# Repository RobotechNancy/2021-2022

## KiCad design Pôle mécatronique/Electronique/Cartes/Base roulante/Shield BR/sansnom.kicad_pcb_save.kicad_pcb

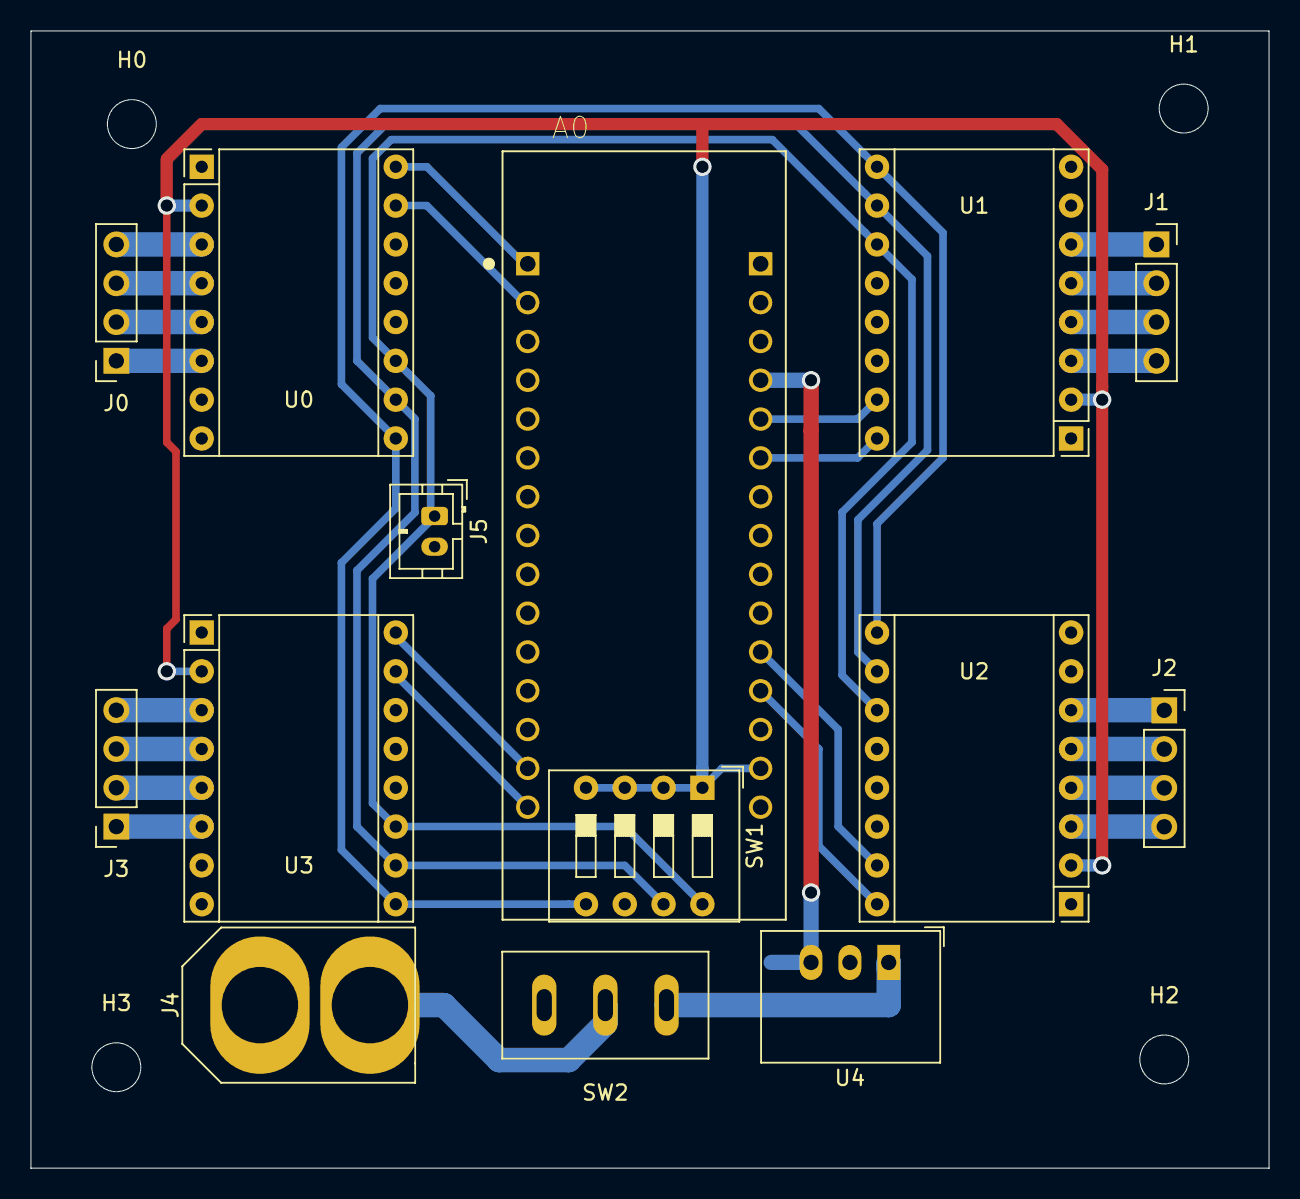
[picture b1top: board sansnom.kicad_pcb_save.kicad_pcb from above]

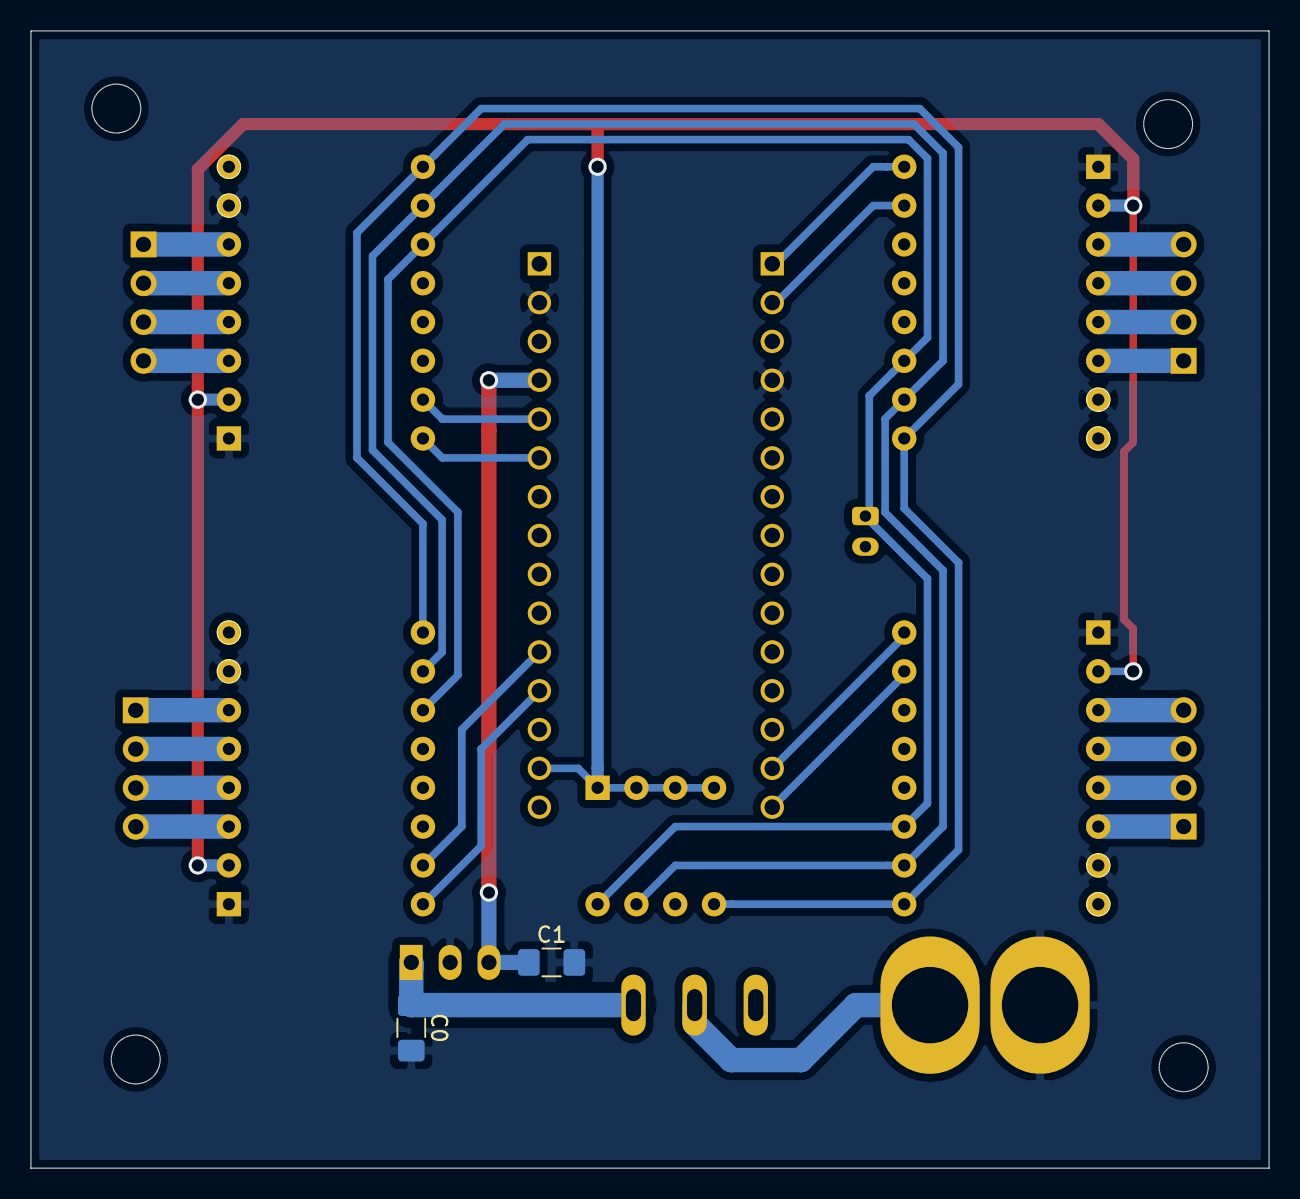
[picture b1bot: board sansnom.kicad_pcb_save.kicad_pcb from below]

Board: 2 copper layers, 81.0 x 74.4 mm, 20 parts (2 on the bottom side), 34 nets.

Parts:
A0: NUCLEO-F303K8; MODULE_NUCLEO-F303K8
C0, C1: 10u; C_1206_3216Metric_Pad1.42x1.75mm_HandSolder
H0, H1, H2, H3: MountingHole; MountingHole_3.2mm_M3
J0, J1, J2, J3: Conn_01x04_Female; PinSocket_1x04_P2.54mm_Vertical
J4: XT60
J5: Conn_01x02_Female; JST_PH_B2B-PH-K_1x02_P2.00mm_Vertical
SW1: SW_DIP_x04; SW_DIP_SPSTx04_Slide_9.78x12.34mm_W7.62mm_P2.54mm
SW2: SW_Push_SPDT; Switch_3_Pin
U0, U1, U2, U3: TMC2208; TMC_2208_BOB
U4: R-78E5.0-0.5; Converter_DCDC_RECOM_R-78E-0.5_THT

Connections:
+5V: A0.4.4, C1.1, U4.3
+BATT: C0.1, SW2.1, U0.8, U1.8, U2.8, U3.8, U4.1
CAN_Rx: A0.3.13, J5.2
CAN_Tx: A0.3.5, J5.1
Dir0: A0.3.1, U0.9
Dir1: A0.4.6, U1.9
Dir2: A0.4.12, U2.9
Dir3: A0.3.14, U3.9
EN: SW1.5, U0.16, U1.16, U2.16, U3.16
GND: A0.3.4, A0.4.2, C0.2, C1.2, J4.1, U0.1, U0.7, U1.1, U1.7, U2.1, U2.7, U3.1, U3.7, U4.2
M1: SW1.7, U0.15, U1.15, U2.15, U3.15
M2: SW1.8, U0.14, U1.14, U2.14, U3.14
unnamed: J0.1, U0.6
unnamed: J0.2, U0.5
unnamed: J0.3, U0.4
unnamed: J0.4, U0.3
unnamed: J1.1, U1.6
unnamed: J1.2, U1.5
unnamed: J1.3, U1.4
unnamed: J1.4, U1.3
unnamed: J2.1, U2.6
unnamed: J2.2, U2.5
unnamed: J2.3, U2.4
unnamed: J2.4, U2.3
unnamed: J3.1, U3.6
unnamed: J3.2, U3.5
unnamed: J3.3, U3.4
unnamed: J3.4, U3.3
unnamed: J4.2, SW2.2
Stp0: A0.3.2, U0.10
Stp1: A0.4.5, U1.10
Stp2: A0.4.11, U2.10
Stp3: A0.3.15, U3.10
Vio: A0.4.14, SW1.1, SW1.2, SW1.3, SW1.4, U0.2, U1.2, U2.2, U3.2

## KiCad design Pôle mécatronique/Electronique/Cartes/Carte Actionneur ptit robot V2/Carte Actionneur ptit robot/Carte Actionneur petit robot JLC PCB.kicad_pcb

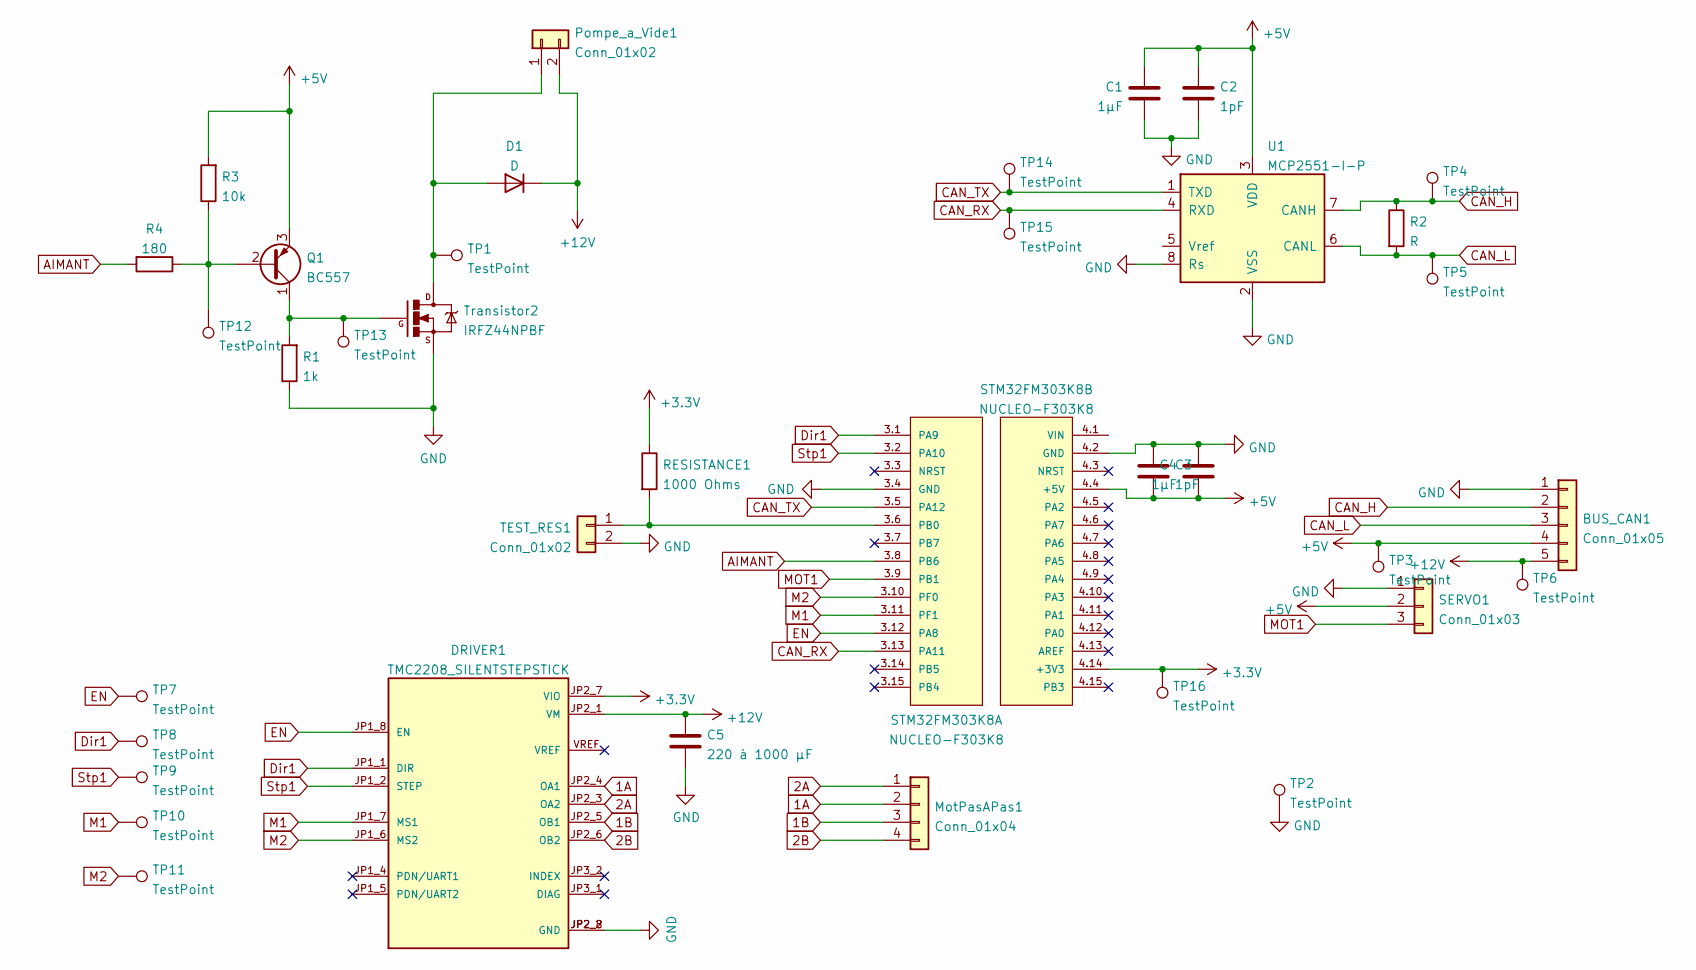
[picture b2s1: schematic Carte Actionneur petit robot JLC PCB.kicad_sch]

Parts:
BUS_CAN1: Conn_01x05; JST_PH_B5B-PH-K_1x05_P2.00mm_Vertical
C1, C4: 1µF; C_1206_3216Metric
C2, C3: 1pF; C_1206_3216Metric
C5: 220 à 1000 µF; CP_Radial_D8.0mm_P3.50mm
D1: D; D_A-405_P12.70mm_Horizontal
DRIVER1: TMC2208_SILENTSTEPSTICK; MODULE_TMC2208_SILENTSTEPSTICK
MotPasAPas1: Conn_01x04; PinSocket_1x04_P2.54mm_Vertical
Pompe_a_Vide1: Conn_01x02; JST_PH_B2B-PH-K_1x02_P2.00mm_Vertical
Q1: BC557; TO-92_Inline
R1: 1k; R_Axial_DIN0207_L6.3mm_D2.5mm_P10.16mm_Horizontal
R2: R; R_Axial_DIN0207_L6.3mm_D2.5mm_P10.16mm_Horizontal
R3: 10k; R_Axial_DIN0207_L6.3mm_D2.5mm_P10.16mm_Horizontal
R4: 180; R_Axial_DIN0207_L6.3mm_D2.5mm_P10.16mm_Horizontal
RESISTANCE1: 1000 Ohms; R_Axial_DIN0207_L6.3mm_D2.5mm_P10.16mm_Horizontal
SERVO1: Conn_01x03; JST_PH_B3B-PH-K_1x03_P2.00mm_Vertical
STM32FM303K8: NUCLEO-F303K8; iou; PARTREV 3
TEST_RES1: Conn_01x02; PinSocket_1x02_P2.54mm_Vertical
TP1, TP2, TP3, TP4, TP5, TP6, TP7, TP8, TP9, TP10, TP11, TP12, TP13, TP14, TP15, TP16: TestPoint; TestPoint_Pad_D2.0mm
Transistor2: IRFZ44NPBF; TO-220-3_Horizontal_TabDown
U1: MCP2551-I-P; DIP-8_W7.62mm

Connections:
1A: DRIVER1.JP2_4 (OA1), MotPasAPas1.2
1B: DRIVER1.JP2_5 (OB1), MotPasAPas1.3
2A: DRIVER1.JP2_3 (OA2), MotPasAPas1.1
2B: DRIVER1.JP2_6 (OB2), MotPasAPas1.4
+3V3: DRIVER1.JP2_7 (VIO), RESISTANCE1.1, STM32FM303K8.4.14 (+3V3), TP16.1
+5V: BUS_CAN1.4, C1.1, C2.1, C3.2, C4.2, Q1.3 (E), R3.2, SERVO1.2, STM32FM303K8.4.4 (+5V), TP3.1, U1.3 (VDD)
+12V: BUS_CAN1.5, C5.1, D1.1 (K), DRIVER1.JP2_1 (VM), Pompe_a_Vide1.2, TP6.1; also elsewhere on the board
AIMANT: R4.2, STM32FM303K8.3.8 (PB6)
CAN_H: BUS_CAN1.2, R2.1, TP4.1, U1.7 (CANH)
CAN_L: BUS_CAN1.3, R2.2, TP5.1, U1.6 (CANL)
CAN_RX: STM32FM303K8.3.13 (PA11), TP15.1, U1.4 (RXD)
CAN_TX: STM32FM303K8.3.5 (PA12), TP14.1, U1.1 (TXD)
Dir1: DRIVER1.JP1_1 (DIR), STM32FM303K8.3.1 (PA9), TP8.1
EN: DRIVER1.JP1_8 (EN), STM32FM303K8.3.12 (PA8), TP7.1
GND: BUS_CAN1.1, C1.2, C2.2, C3.1, C4.1, C5.2, DRIVER1.JP2_2 (GND), DRIVER1.JP2_8 (GND), R1.1, SERVO1.1, STM32FM303K8.3.4 (GND), STM32FM303K8.4.2 (GND), TEST_RES1.2, TP2.1, Transistor2.3, U1.2 (VSS), U1.8 (Rs)
M1: DRIVER1.JP1_7 (MS1), STM32FM303K8.3.11 (PF1), TP10.1
M2: DRIVER1.JP1_6 (MS2), STM32FM303K8.3.10 (PF0), TP11.1
MOT1: SERVO1.3, STM32FM303K8.3.9 (PB1)
unnamed 18: D1.2 (A), Pompe_a_Vide1.1, TP1.1, Transistor2.2; also elsewhere on the board
unnamed: Q1.1 (C), R1.2, TP13.1, Transistor2.1
unnamed: Q1.2 (B), R3.1, R4.1, TP12.1
unnamed: RESISTANCE1.2, STM32FM303K8.3.6 (PB0), TEST_RES1.1
Stp1: DRIVER1.JP1_2 (STEP), STM32FM303K8.3.2 (PA10), TP9.1

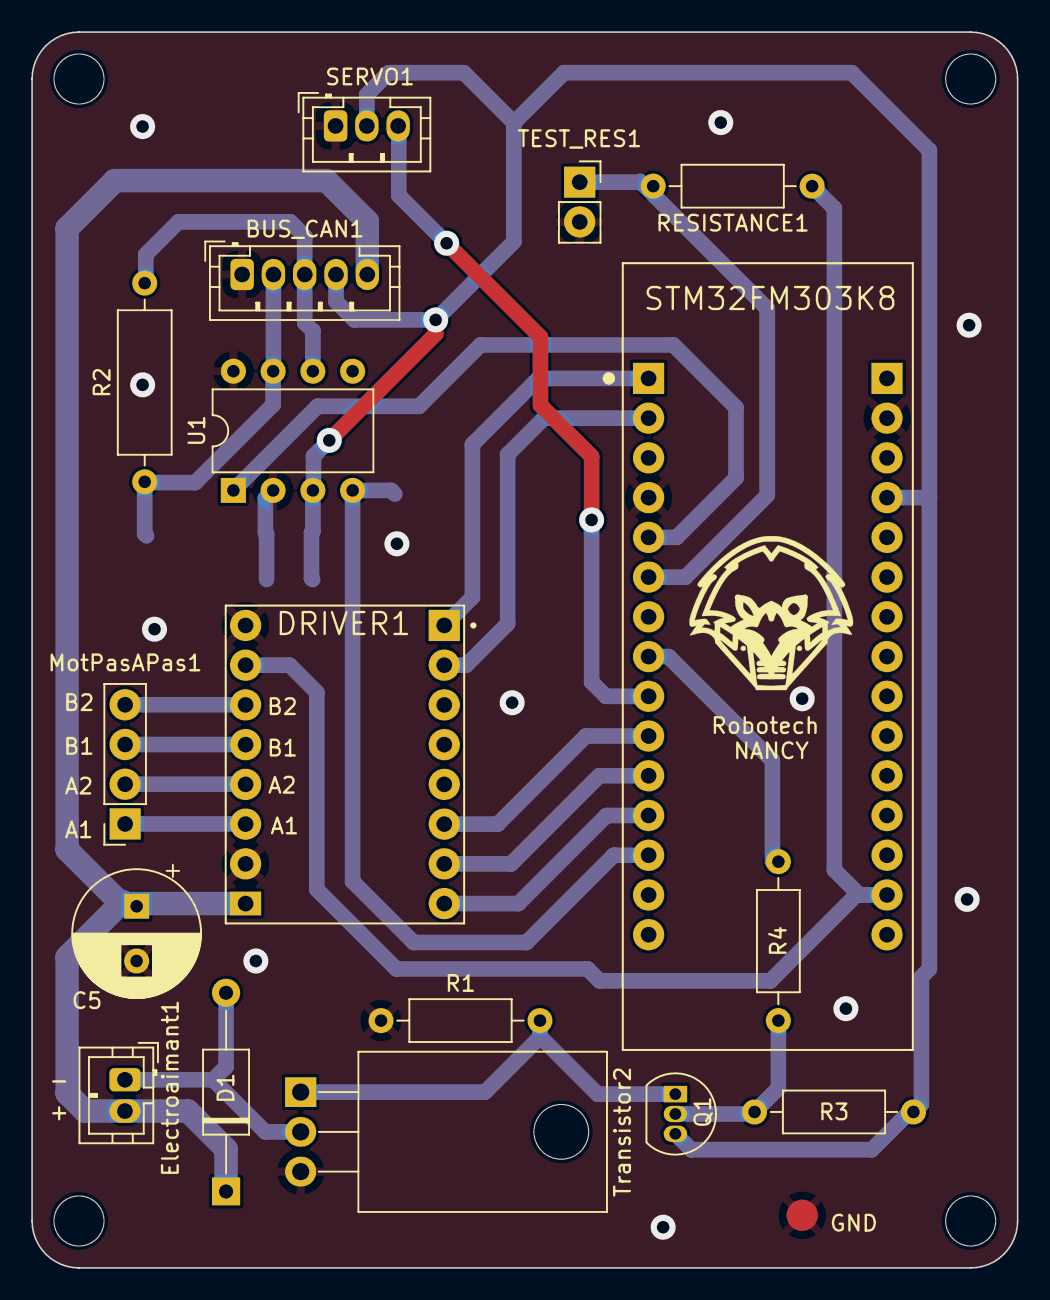
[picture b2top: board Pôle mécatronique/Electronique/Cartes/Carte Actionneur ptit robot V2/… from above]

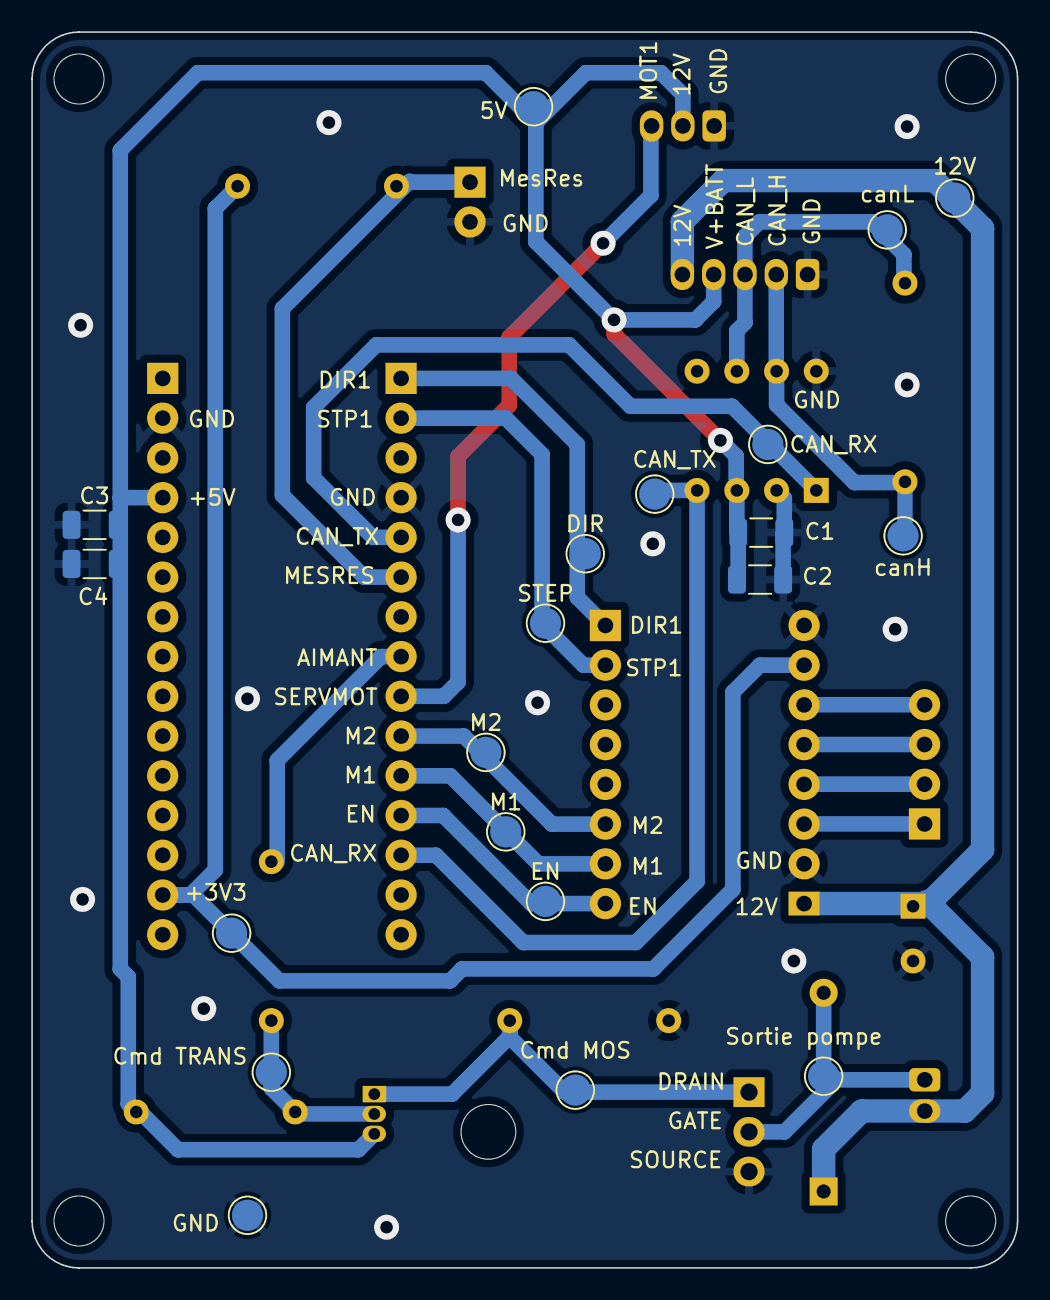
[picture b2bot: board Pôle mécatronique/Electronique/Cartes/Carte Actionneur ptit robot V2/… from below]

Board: 2 copper layers, 63.0 x 79.0 mm, 37 parts (20 on the bottom side), 23 nets.

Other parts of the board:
Electroaimant1: Conn_01x02; JST_PH_B2B-PH-K_1x02_P2.00mm_Vertical

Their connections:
+12V: Electroaimant1.2; also elsewhere on the board
unnamed 18: Electroaimant1.1; also elsewhere on the board

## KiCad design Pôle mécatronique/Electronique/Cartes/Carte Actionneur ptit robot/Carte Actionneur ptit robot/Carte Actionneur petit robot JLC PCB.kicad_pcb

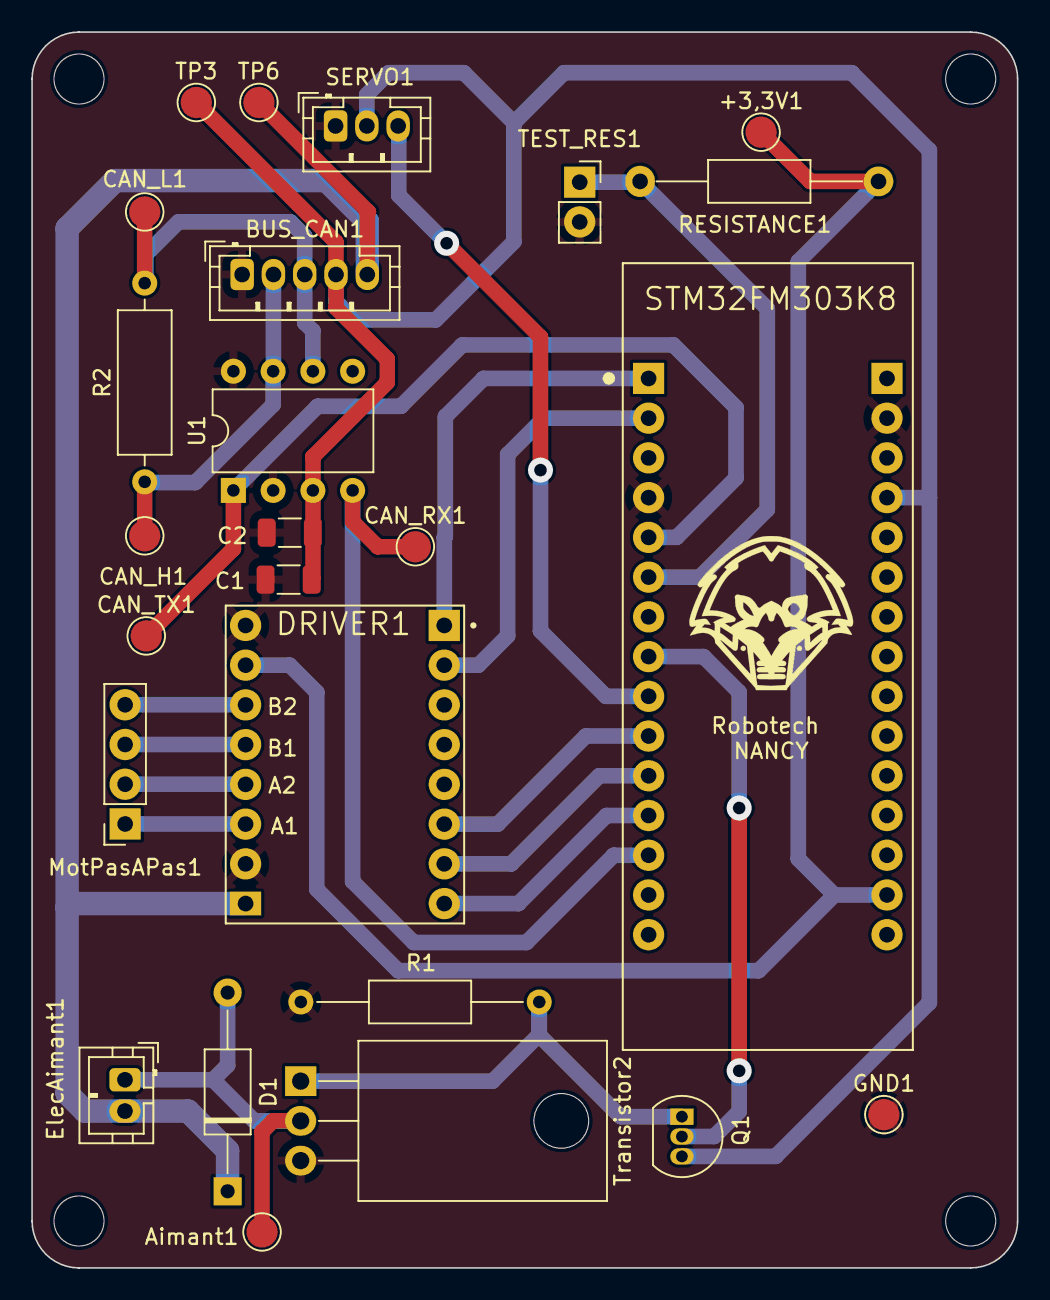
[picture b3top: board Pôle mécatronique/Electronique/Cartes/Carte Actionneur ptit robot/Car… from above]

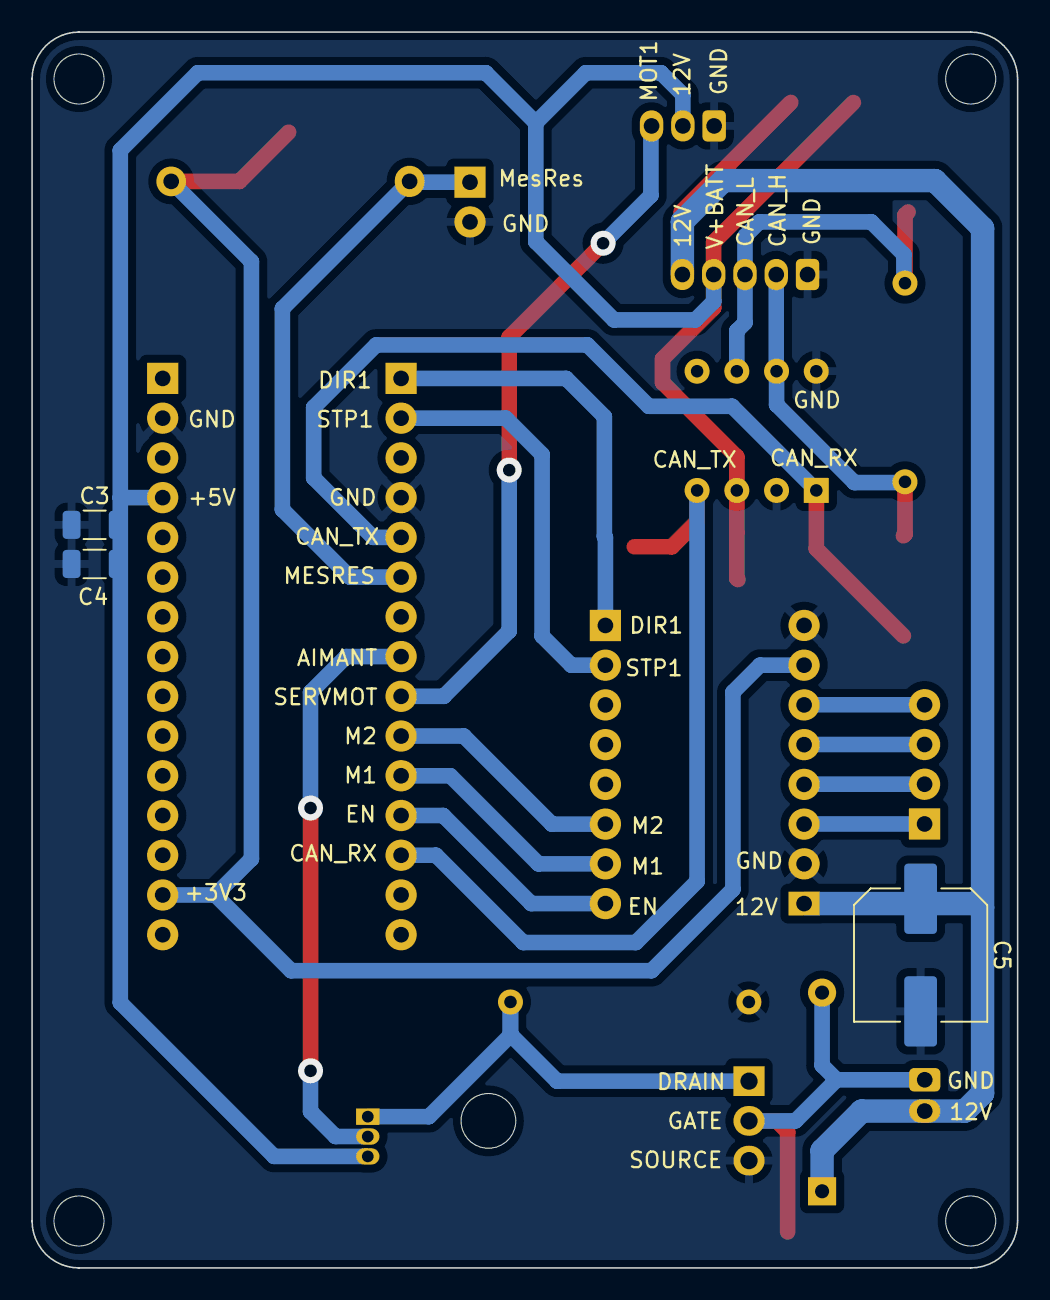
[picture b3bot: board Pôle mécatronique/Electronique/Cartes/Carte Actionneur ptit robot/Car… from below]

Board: 2 copper layers, 63.0 x 79.0 mm, 28 parts (3 on the bottom side), 22 nets.

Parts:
+3,3V1: TestPoint; TestPoint_Pad_D2.0mm
Aimant1: TestPoint; TestPoint_Pad_D2.0mm
BUS_CAN1: Conn_01x05; JST_PH_B5B-PH-K_1x05_P2.00mm_Vertical
C1, C4: 1µF; C_1206_3216Metric
C2, C3: 1pF; C_1206_3216Metric
C5: 220 à 1000 µF; C_Elec_8x10.2
CAN_H1: TestPoint; TestPoint_Pad_D2.0mm
CAN_L1: TestPoint; TestPoint_Pad_D2.0mm
CAN_RX1: TestPoint; TestPoint_Pad_D2.0mm
CAN_TX1: TestPoint; TestPoint_Pad_D2.0mm
D1: D; D_A-405_P12.70mm_Horizontal
DRIVER1: TMC2208_SILENTSTEPSTICK; MODULE_TMC2208_SILENTSTEPSTICK
ElecAimant1: Conn_01x02; JST_PH_B2B-PH-K_1x02_P2.00mm_Vertical
GND1: TestPoint; TestPoint_Pad_D2.0mm
MotPasAPas1: Conn_01x04; PinSocket_1x04_P2.54mm_Vertical
Q1: BC557; TO-92_Inline
R1: R; R_Axial_DIN0207_L6.3mm_D2.5mm_P15.24mm_Horizontal
R2: R; R_Axial_DIN0309_L9.0mm_D3.2mm_P12.70mm_Horizontal
RESISTANCE1: 1000 Ohms; R_Axial_DIN0207_L6.3mm_D2.5mm_P15.24mm_Horizontal
SERVO1: Conn_01x03; JST_PH_B3B-PH-K_1x03_P2.00mm_Vertical
STM32FM303K8: NUCLEO-F303K8; MODULE_NUCLEO-F303K8
TEST_RES1: Conn_01x02; PinSocket_1x02_P2.54mm_Vertical
TP3, TP6: TestPoint; TestPoint_Pad_D2.0mm
Transistor2: IRFZ44NPBF; TO-220-3_Horizontal_TabDown
U1: MCP2551-I-P; DIP-8_W7.62mm

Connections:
1A: DRIVER1.JP2_4 (OA1), MotPasAPas1.2
1B: DRIVER1.JP2_5 (OB1), MotPasAPas1.3
2A: DRIVER1.JP2_3 (OA2), MotPasAPas1.1
2B: DRIVER1.JP2_6 (OB2), MotPasAPas1.4
+3V3: +3,3V1.1, DRIVER1.JP2_7 (VIO), RESISTANCE1.1, STM32FM303K8.4.14 (+3V3)
+5V: BUS_CAN1.4, C1.1, C2.1, C3.2, C4.2, Q1.3 (E), SERVO1.2, STM32FM303K8.4.4 (+5V), TP3.1, U1.3 (VDD)
+12V: BUS_CAN1.5, C5.1, D1.1 (K), DRIVER1.JP2_1 (VM), ElecAimant1.2, TP6.1
AIMANT: Q1.2 (B), STM32FM303K8.3.8 (PB6)
CAN_H: BUS_CAN1.2, CAN_H1.1, R2.1, U1.7 (CANH)
CAN_L: BUS_CAN1.3, CAN_L1.1, R2.2, U1.6 (CANL)
CAN_RX: CAN_RX1.1, STM32FM303K8.3.13 (PA11), U1.4 (RXD)
CAN_TX: CAN_TX1.1, STM32FM303K8.3.5 (PA12), U1.1 (TXD)
Dir1: DRIVER1.JP1_1 (DIR), STM32FM303K8.3.1 (PA9)
EN: DRIVER1.JP1_8 (EN), STM32FM303K8.3.12 (PA8)
GND: BUS_CAN1.1, C1.2, C2.2, C3.1, C4.1, C5.2, DRIVER1.JP2_2 (GND), DRIVER1.JP2_8 (GND), GND1.1, R1.1, SERVO1.1, STM32FM303K8.3.4 (GND), STM32FM303K8.4.2 (GND), TEST_RES1.2, Transistor2.3, U1.2 (VSS), U1.8 (Rs)
M1: DRIVER1.JP1_7 (MS1), STM32FM303K8.3.11 (PF1)
M2: DRIVER1.JP1_6 (MS2), STM32FM303K8.3.10 (PF0)
MOT1: SERVO1.3, STM32FM303K8.3.9 (PB1)
unnamed: Aimant1.1, D1.2 (A), ElecAimant1.1, Transistor2.2
unnamed: Q1.1 (C), R1.2, Transistor2.1
unnamed: RESISTANCE1.2, STM32FM303K8.3.6 (PB0), TEST_RES1.1
Stp1: DRIVER1.JP1_2 (STEP), STM32FM303K8.3.2 (PA10)

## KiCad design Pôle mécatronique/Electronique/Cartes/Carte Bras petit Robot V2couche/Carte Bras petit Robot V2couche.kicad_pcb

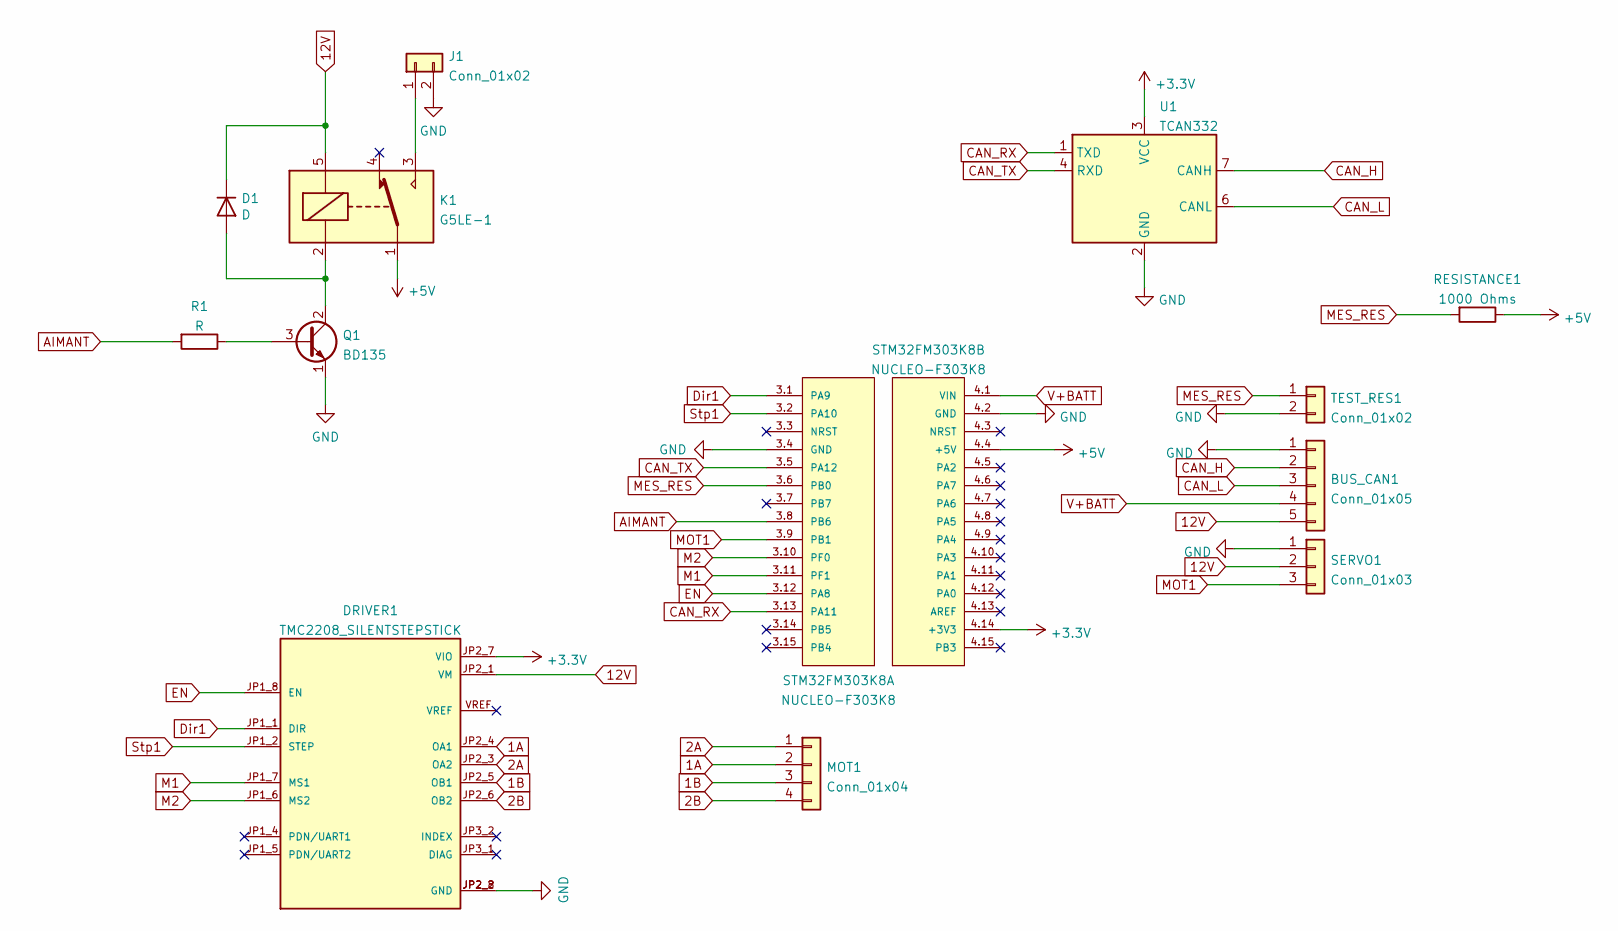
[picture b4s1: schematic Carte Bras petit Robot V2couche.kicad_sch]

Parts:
BUS_CAN1: Conn_01x05; JST_PH_B5B-PH-K_1x05_P2.00mm_Vertical
D1: D; D_DO-15_P12.70mm_Horizontal
DRIVER1: TMC2208_SILENTSTEPSTICK; MODULE_TMC2208_SILENTSTEPSTICK
J1: Conn_01x02; JST_PH_B2B-PH-K_1x02_P2.00mm_Vertical
K1: G5LE-1; Relay_SPDT_Omron-G5LE-1
MOT1: Conn_01x04; PinSocket_1x04_P2.54mm_Vertical
Q1: BD135; TO-126-3_Vertical
R1: R; R_Axial_DIN0207_L6.3mm_D2.5mm_P10.16mm_Horizontal
RESISTANCE1: 1000 Ohms; R_Axial_DIN0207_L6.3mm_D2.5mm_P15.24mm_Horizontal
SERVO1: Conn_01x03; JST_PH_B3B-PH-K_1x03_P2.00mm_Vertical
STM32FM303K8: NUCLEO-F303K8; MODULE_NUCLEO-F303K8; PARTREV 3
TEST_RES1: Conn_01x02; PinSocket_1x02_P2.54mm_Vertical
U1: TCAN332; SO-8_S

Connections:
1A: DRIVER1.JP2_4 (OA1), MOT1.2
1B: DRIVER1.JP2_5 (OB1), MOT1.3
2A: DRIVER1.JP2_3 (OA2), MOT1.1
2B: DRIVER1.JP2_6 (OB2), MOT1.4
12V: BUS_CAN1.5, D1.1 (K), DRIVER1.JP2_1 (VM), K1.5, SERVO1.2
+3V3: DRIVER1.JP2_7 (VIO), STM32FM303K8.4.14 (+3V3), U1.3 (VCC)
+5V: K1.1, RESISTANCE1.1, STM32FM303K8.4.4 (+5V)
AIMANT: R1.2, STM32FM303K8.3.8 (PB6)
CAN_H: BUS_CAN1.2, U1.7 (CANH)
CAN_L: BUS_CAN1.3, U1.6 (CANL)
CAN_RX: STM32FM303K8.3.13 (PA11), U1.1 (TXD)
CAN_TX: STM32FM303K8.3.5 (PA12), U1.4 (RXD)
Dir1: DRIVER1.JP1_1 (DIR), STM32FM303K8.3.1 (PA9)
EN: DRIVER1.JP1_8 (EN), STM32FM303K8.3.12 (PA8)
GND: BUS_CAN1.1, DRIVER1.JP2_2 (GND), DRIVER1.JP2_8 (GND), J1.2, Q1.1 (E), SERVO1.1, STM32FM303K8.3.4 (GND), STM32FM303K8.4.2 (GND), TEST_RES1.2, U1.2 (GND)
M1: DRIVER1.JP1_7 (MS1), STM32FM303K8.3.11 (PF1)
M2: DRIVER1.JP1_6 (MS2), STM32FM303K8.3.10 (PF0)
MES_RES: RESISTANCE1.2, STM32FM303K8.3.6 (PB0), TEST_RES1.1
MOT1: SERVO1.3, STM32FM303K8.3.9 (PB1)
unnamed: D1.2 (A), K1.2, Q1.2 (C)
unnamed: J1.1, K1.3
unnamed: Q1.3 (B), R1.1
Stp1: DRIVER1.JP1_2 (STEP), STM32FM303K8.3.2 (PA10)
V+BATT: BUS_CAN1.4, STM32FM303K8.4.1 (VIN)

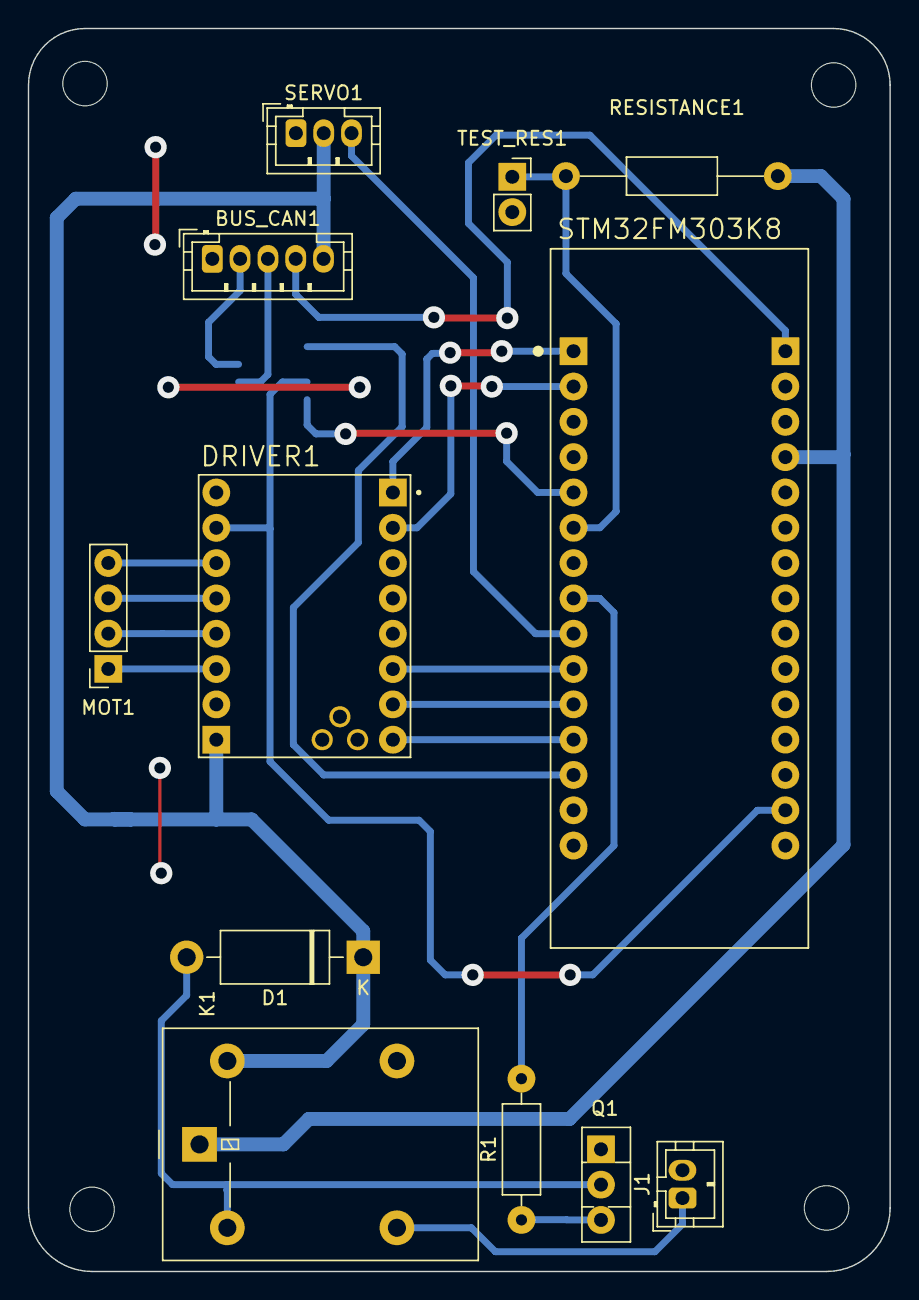
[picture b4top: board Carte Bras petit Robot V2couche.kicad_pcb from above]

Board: 2 copper layers, 62.0 x 89.4 mm, 13 parts (1 on the bottom side), 24 nets.

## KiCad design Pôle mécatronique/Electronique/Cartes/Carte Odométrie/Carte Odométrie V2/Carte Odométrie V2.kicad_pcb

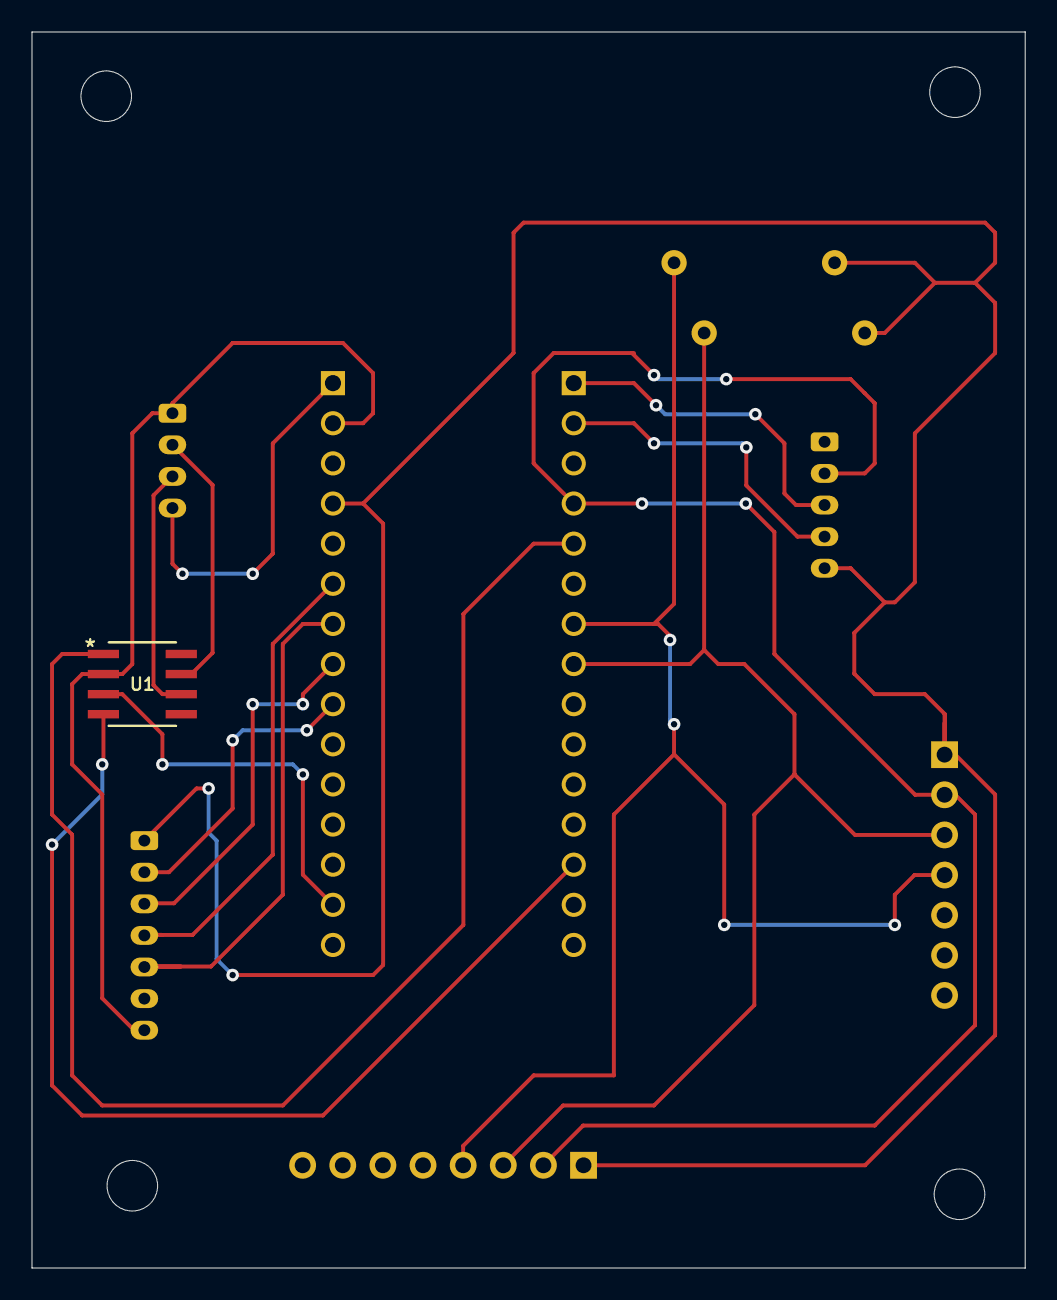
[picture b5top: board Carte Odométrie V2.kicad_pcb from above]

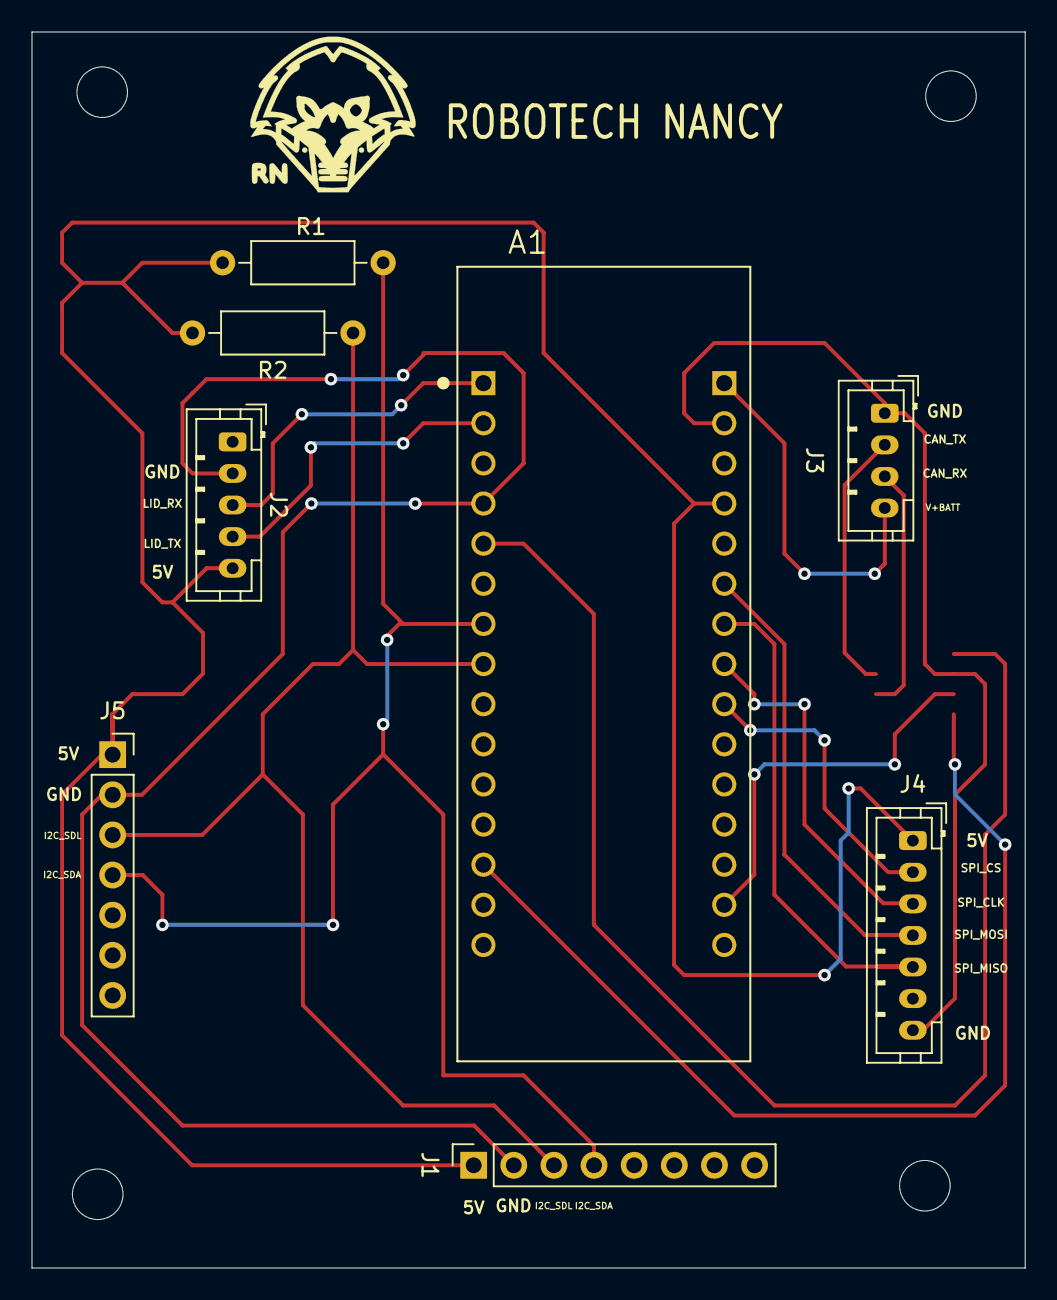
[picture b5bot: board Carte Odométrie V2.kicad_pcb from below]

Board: 2 copper layers, 62.9 x 78.2 mm, 13 parts (8 on the bottom side), 16 nets.

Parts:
A1: NUCLEO-F303K8; MODULE_NUCLEO-F303K8
J1: Conn_01x08; PinSocket_1x08_P2.54mm_Vertical
J2: Conn_01x05; JST_PH_B5B-PH-K_1x05_P2.00mm_Vertical
J3: Conn_01x04; JST_PH_B4B-PH-K_1x04_P2.00mm_Vertical
J4: Conn_01x07; JST_PH_B7B-PH-K_1x07_P2.00mm_Vertical
J5: Conn_01x07; PinSocket_1x07_P2.54mm_Vertical
R1, R2: 10000ohm; R_Axial_DIN0207_L6.3mm_D2.5mm_P10.16mm_Horizontal
REF: MountingHole_3.2mm_M3
REF#2, REF#3, REF#4: MountingHole_3.2mm_M3
U1: TCAN332; SO-8_S

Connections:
+3V3: A1.4.14 (+3V3), U1.3 (VCC)
+5V: A1.4.4 (+5V), J1.1, J2.5, J4.1, J5.1, R1.1, R2.2
+BATT: A1.4.1 (VIN), J3.4
CAN_H: J3.2, U1.7 (CANH)
CAN_L: J3.3, U1.6 (CANL)
CAN_RX: A1.3.5 (PA12), U1.1 (TXD)
CAN_TX: A1.3.13 (PA11), U1.4 (RXD)
GND: A1.3.4 (GND), A1.4.2 (GND), J1.2, J2.2, J3.1, J4.7, J5.2, U1.2 (GND)
I2C_SCL: A1.3.8 (PB6), J1.3, J5.3, R2.1
I2C_SDA: A1.3.7 (PB7), J1.4, J5.4, R1.2
SPI_CLK: A1.4.8 (PA5), J4.3
SPI_CS: A1.4.9 (PA4), J4.2
SPI_MISO: A1.4.7 (PA6), J4.5
SPI_MOSI: A1.4.6 (PA7), J4.4
UART1_RX: A1.3.2 (PA10), J2.4
UART1_TX: A1.3.1 (PA9), J2.3

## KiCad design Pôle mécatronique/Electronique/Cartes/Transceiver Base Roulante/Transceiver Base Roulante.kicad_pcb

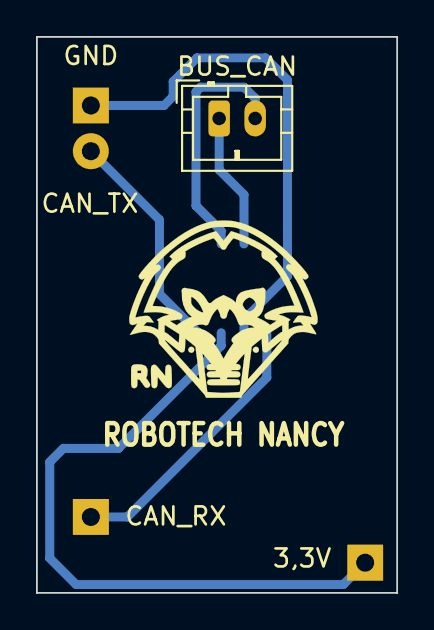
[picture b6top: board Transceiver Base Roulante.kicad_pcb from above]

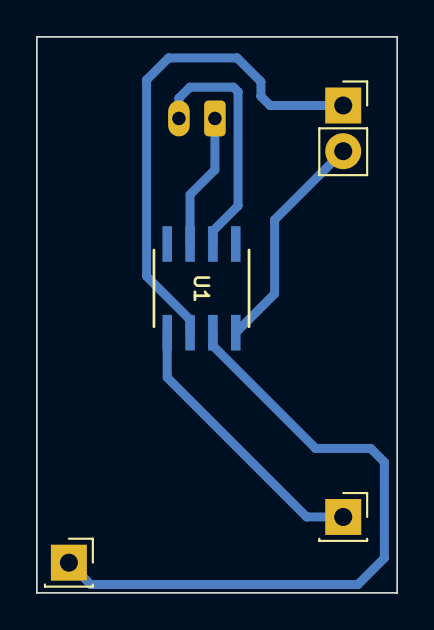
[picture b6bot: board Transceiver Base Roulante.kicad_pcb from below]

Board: 2 copper layers, 20.0 x 30.9 mm, 5 parts (4 on the bottom side), 6 nets.

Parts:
3,3V: Conn_01x01; PinSocket_1x01_P2.54mm_Vertical
BUS_CAN: Conn_01x02; JST_PH_B2B-PH-K_1x02_P2.00mm_Vertical
CAN_RX: Conn_01x01; PinSocket_1x01_P2.54mm_Vertical
GND: Conn_01x02; PinSocket_1x02_P2.54mm_Vertical
U1: TCAN332; SO-8_S

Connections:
+3V3: 3,3V.1, U1.3 (VCC)
CAN_H: BUS_CAN.1, U1.7 (CANH)
CAN_L: BUS_CAN.2, U1.6 (CANL)
CAN_RX: CAN_RX.1, U1.1 (TXD)
CAN_TX: GND.2, U1.4 (RXD)
GND: GND.1, U1.2 (GND)
